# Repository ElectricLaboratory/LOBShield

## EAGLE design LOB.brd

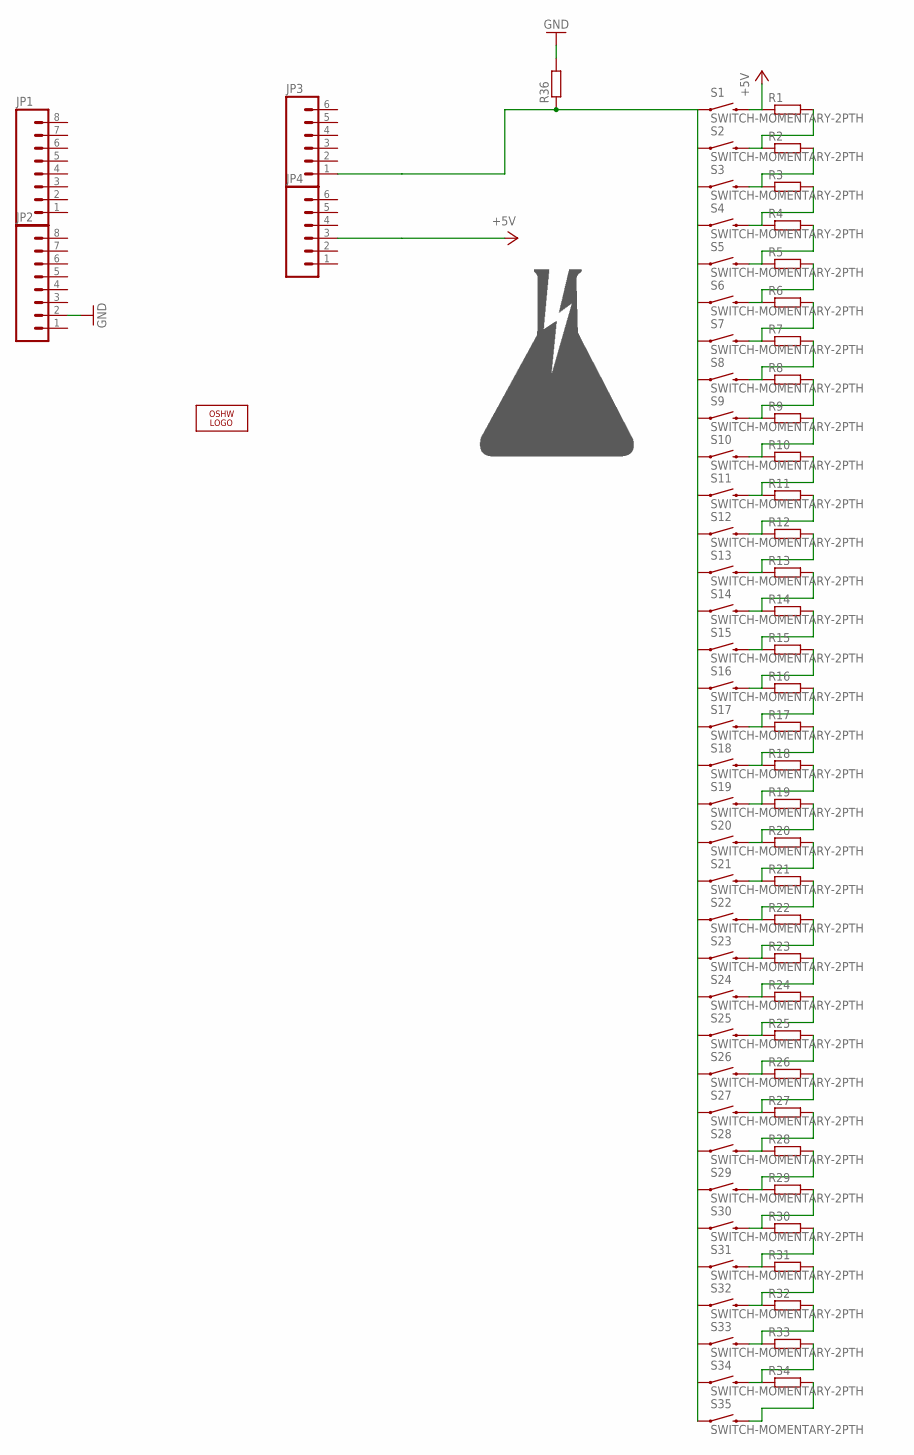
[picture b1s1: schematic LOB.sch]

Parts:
JP1, JP2: M081X08; 1X08
JP3, JP4: M06SIP; 1X06
LOGO1: LOGO-OSHW-10MILX0200-NT; OSHW_10X200_NOTEXT
R1, R2, R3, R4, R5, R6, R7, R8, R9, R10, R11, R12, R13, R14, R15, R16, R17, R18, R19, R20, R21, R22, R23, R24, R25, R26, R27, R28, R29, R30, R31, R32, R33, R34, R36: R-EU_0204/7; 0204/7
S1, S2, S3, S4, S5, S6, S7, S8, S9, S10, S11, S12, S13, S14, S15, S16, S17, S18, S19, S20, S21, S22, S23, S24, S25, S26, S27, S28, S29, S30, S31, S32, S33, S34, S35: SWITCH-MOMENTARY-2PTH; TACTILE-PTH
U$1: EL-LOGO

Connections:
+5V: JP4.3, R1.1, S1.3 (2)
GND: JP2.2, R36.2
unnamed: JP3.1, R36.1, S1.1, S2.1, S3.1, S4.1, S5.1, S6.1, S7.1, S8.1, S9.1, S10.1, S11.1, S12.1, S13.1, S14.1, S15.1, S16.1, S17.1, S18.1, S19.1, S20.1, S21.1, S22.1, S23.1, S24.1, S25.1, S26.1, S27.1, S28.1, S29.1, S30.1, S31.1, S32.1, S33.1, S34.1, S35.1
unnamed: R1.2, R2.1, S2.3 (2)
unnamed: R2.2, R3.1, S3.3 (2)
unnamed: R3.2, R4.1, S4.3 (2)
unnamed: R4.2, R5.1, S5.3 (2)
unnamed: R5.2, R6.1, S6.3 (2)
unnamed: R6.2, R7.1, S7.3 (2)
unnamed: R7.2, R8.1, S8.3 (2)
unnamed: R8.2, R9.1, S9.3 (2)
unnamed: R9.2, R10.1, S10.3 (2)
unnamed: R10.2, R11.1, S11.3 (2)
unnamed: R11.2, R12.1, S12.3 (2)
unnamed: R12.2, R13.1, S13.3 (2)
unnamed: R13.2, R14.1, S14.3 (2)
unnamed: R14.2, R15.1, S15.3 (2)
unnamed: R15.2, R16.1, S16.3 (2)
unnamed: R16.2, R17.1, S17.3 (2)
unnamed: R17.2, R18.1, S18.3 (2)
unnamed: R18.2, R19.1, S19.3 (2)
unnamed: R19.2, R20.1, S20.3 (2)
unnamed: R20.2, R21.1, S21.3 (2)
unnamed: R21.2, R22.1, S22.3 (2)
unnamed: R22.2, R23.1, S23.3 (2)
unnamed: R23.2, R24.1, S24.3 (2)
unnamed: R24.2, R25.1, S25.3 (2)
unnamed: R25.2, R26.1, S26.3 (2)
unnamed: R26.2, R27.1, S27.3 (2)
unnamed: R27.2, R28.1, S28.3 (2)
unnamed: R28.2, R29.1, S29.3 (2)
unnamed: R29.2, R30.1, S30.3 (2)
unnamed: R30.2, R31.1, S31.3 (2)
unnamed: R31.2, R32.1, S32.3 (2)
unnamed: R32.2, R33.1, S33.3 (2)
unnamed: R33.2, R34.1, S34.3 (2)
unnamed: R34.2, S35.3 (2)

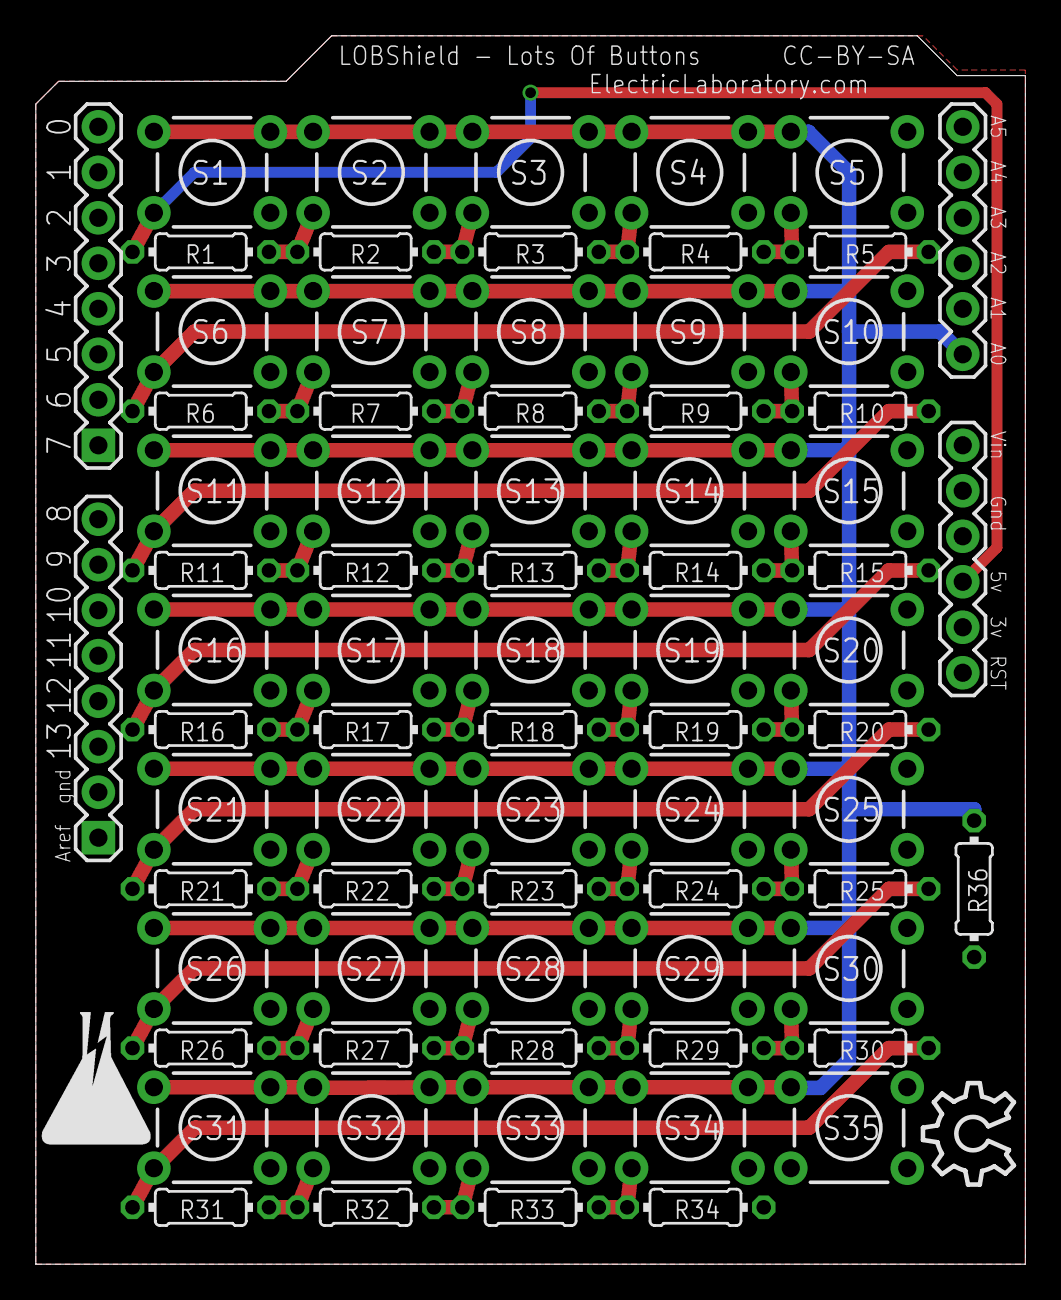
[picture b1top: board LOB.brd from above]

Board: 2 copper layers, 55.2 x 68.6 mm, 76 parts (0 on the bottom side), 37 nets.

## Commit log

2013-06-15 Add PDFs

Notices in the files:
LOB.brd:
CC-BY-SA
parts and their libraries:
SparkFun-Electromechanical: Licensing: CC v3.0 Share-Alike You are welcome to use this library for commercial purposes.
